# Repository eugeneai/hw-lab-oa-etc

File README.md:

# hw-lab-oa-etc
PCB for laboratory works on temerature sensor, generators and ADC, etc.

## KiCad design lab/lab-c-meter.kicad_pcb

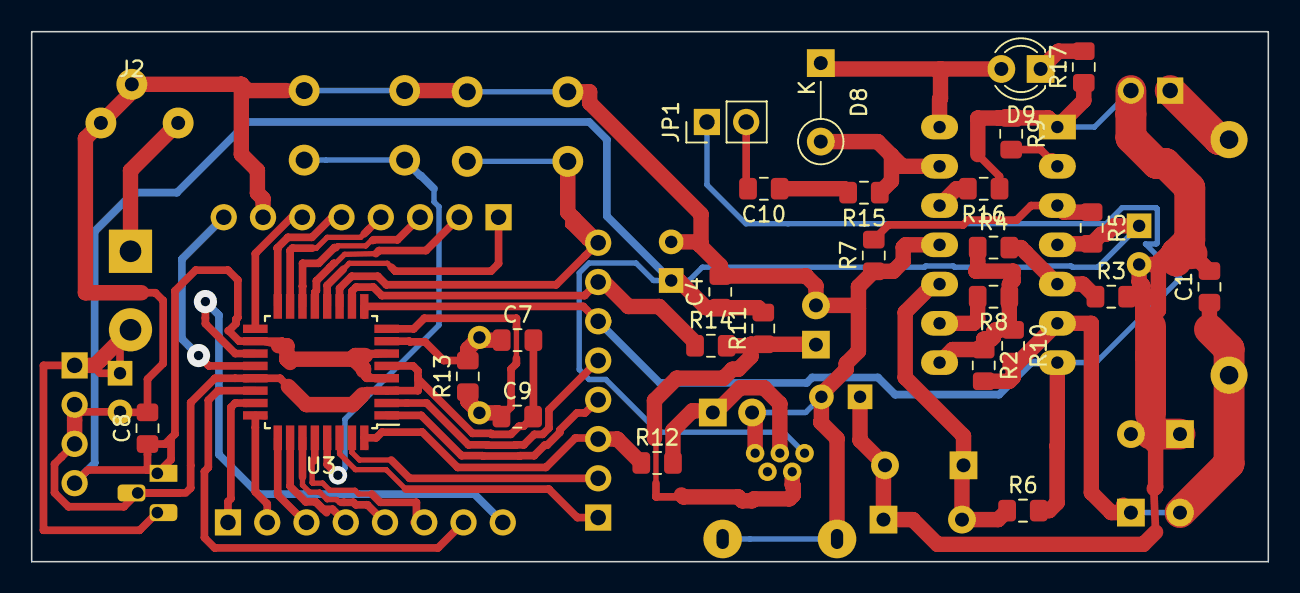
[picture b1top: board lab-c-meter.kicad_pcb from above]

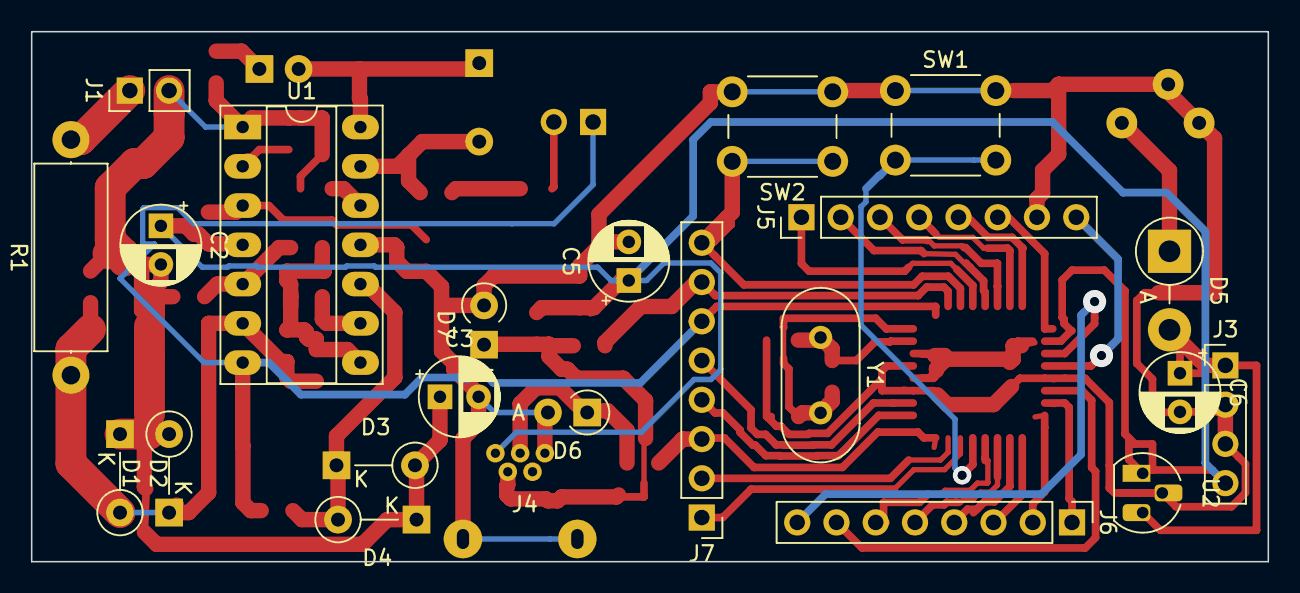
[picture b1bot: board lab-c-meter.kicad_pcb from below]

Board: 2 copper layers, 80.0 x 34.3 mm, 50 parts (23 on the bottom side), 47 nets.

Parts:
C1: 22n; C_0805_2012Metric_Pad1.15x1.40mm_HandSolder
C2, C3: 220u 6.3V; CP_Radial_D5.0mm_P2.50mm
C4, C8, C10: 100n; C_0805_2012Metric_Pad1.15x1.40mm_HandSolder
C5, C6: 4u7 6.3V; CP_Radial_D5.0mm_P2.50mm
C7, C9: 22p; C_0805_2012Metric_Pad1.15x1.40mm_HandSolder
D1, D2: HER105; D_A-405_P5.08mm_Vertical_KathodeUp
D3, D4, D8: 4148; D_A-405_P5.08mm_Vertical_KathodeUp
D5: M7; D_5W_P5.08mm_Vertical_AnodeUp
D6: 3v6; D_A-405_P2.54mm_Vertical_AnodeUp
D7: 3v6; D_A-405_P2.54mm_Vertical_KathodeUp
D9: AC; LED_D3.0mm
J1: IN; PinHeader_1x02_P2.54mm_Vertical
J2: Barrel_Jack_Switch; Barrel-little-11mm-x-5mm
J3: Conn_01x04; PinHeader_1x04_P2.54mm_Vertical
J4: USB_B_Mini; USB-mini-S2126.12010-Circular
J5: PB; PinHeader_1x08_P2.54mm_Vertical
J6: PC; PinHeader_1x08_P2.54mm_Vertical
J7: PD; PinHeader_1x08_P2.54mm_Vertical
JP1: WATCH; PinHeader_1x02_P2.54mm_Vertical
R1: 0.33 0.5W; R_Axial_DIN0414_L11.9mm_D4.5mm_P15.24mm_Horizontal
R2: 3K3; R_0805_2012Metric_Pad1.15x1.40mm_HandSolder
R3: 11K; R_0805_2012Metric_Pad1.15x1.40mm_HandSolder
R4, R5, R7: 100K; R_0805_2012Metric_Pad1.15x1.40mm_HandSolder
R6: 10K; R_0805_2012Metric_Pad1.15x1.40mm_HandSolder
R8, R9, R16: 4K7; R_0805_2012Metric_Pad1.15x1.40mm_HandSolder
R10: 1K0; R_0805_2012Metric_Pad1.15x1.40mm_HandSolder
R11: 1k5; R_0805_2012Metric_Pad1.15x1.40mm_HandSolder
R12, R14: 68R; R_0805_2012Metric_Pad1.15x1.40mm_HandSolder
R13: 1M; R_0805_2012Metric_Pad1.15x1.40mm_HandSolder
R15: 10k; R_0805_2012Metric_Pad1.15x1.40mm_HandSolder
R17: 10R; R_0805_2012Metric_Pad1.15x1.40mm_HandSolder
SW1: RST; SW_PUSH_6mm
SW2: BLD; SW_PUSH_6mm
U1: LM324; DIP-14_W7.62mm_Socket_LongPads
U2: L78L05_TO92; TO-92_HandSolder
U3: ATmega8-16AU; TQFP-32_7x7mm_P0.8mm
Y1: 16MHz; Crystal_HC49-U_Vertical

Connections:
+5V: C2.1, C4.1, C5.1, C8.1, J3.4, J4.1, R5.2, R11.2, U1.4, U2.1, U3.4, U3.6, U3.18
ADC6: J6.8, U3.19
ADC7: J6.7, U3.22
AREF: J5.8, U3.20
CNT: J7.6, JP1.1, R6.2, U1.7, U3.9
D+: J7.3, R12.1, U3.32
D-: J7.7, R14.1, U3.10
GND: C3.2, C4.2, C5.2, C6.2, C7.2, C8.2, C9.2, D6.2, D7.2, J2.2, J2.3, J3.2, J3.3, J4.5, J4.6, J5.7, R7.1, SW1.1, SW2.2, U1.11, U2.2, U3.3, U3.5, U3.21
MID: C1.2, C2.2, C3.1, D1.2, D2.1, D3.2, D4.1, J1.2, R3.2, R9.1, R16.1, R17.1, U1.1
MISO: J5.5, U3.16
MOSI: J5.4, U3.15
unnamed: C1.1, D1.1, D2.2, R1.1, R2.2, R10.2, U1.6
unnamed: C7.1, R13.2, U3.7, Y1.1
unnamed: C9.1, R13.1, U3.8, Y1.2
unnamed: C10.1, R15.2
unnamed: C10.2, JP1.2
unnamed: D3.1, D4.2, R6.1, U1.10
unnamed: D5.1, J2.1
unnamed: D6.1, J4.3, R12.2
unnamed: D7.1, J4.2, R11.1, R14.2
unnamed: D8.1, D9.2, U1.14
unnamed: D8.2, R15.1, U1.13
unnamed: D9.1, R17.2
unnamed: J1.1, R1.2
unnamed: J5.1, U3.12
unnamed: J5.2, U3.13
unnamed: R3.1, R4.2, U1.5
unnamed: R5.1, R7.2, U1.3
unnamed: R8.2, U1.9
unnamed: R9.2, U1.2
unnamed: R2.1, R4.1, R8.1, R10.1, U1.8
unnamed: R16.2, U1.12
PC0: J6.1, U3.23
PC1: J6.2, U3.24
PC2: J6.3, U3.25
PC3: J6.4, U3.26
PC4: J6.5, U3.27
PC5: J6.6, U3.28
PD0: J7.1, U3.30
PD1: J7.2, U3.31
PD3: J7.4, U3.1
PD4: J7.5, U3.2
PD7: J7.8, SW2.1, U3.11
SCK: J5.6, U3.17
SS: J5.3, U3.14
VIN: C6.1, D5.2, J3.1, U2.3
~RESET: SW1.2, U3.29

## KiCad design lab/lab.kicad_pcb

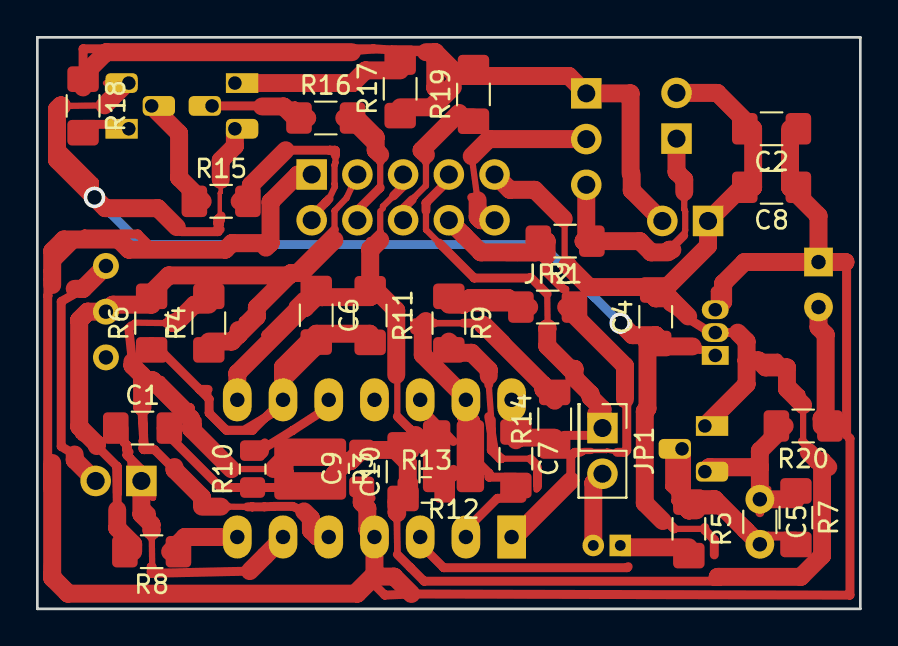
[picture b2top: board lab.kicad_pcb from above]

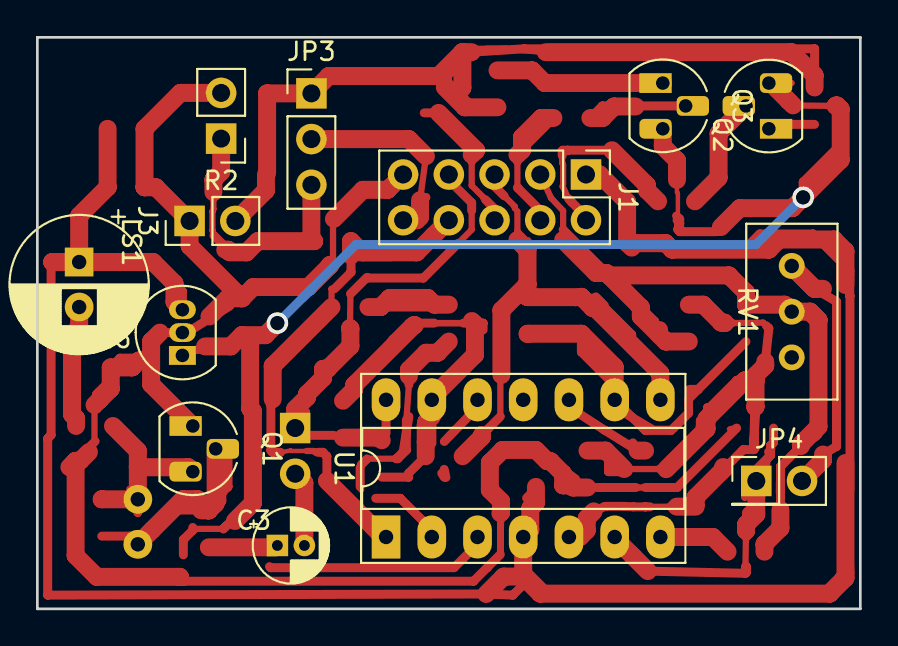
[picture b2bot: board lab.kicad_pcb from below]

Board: 2 copper layers, 45.7 x 31.8 mm, 43 parts (13 on the bottom side), 31 nets.

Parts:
C1, C2, C4: 1u; C_1206_3216Metric_Pad1.42x1.75mm_HandSolder
C3: 5u 5V; CP_Radial_D4.0mm_P1.50mm
C5: 6u8; C_Disc_D3.0mm_W1.6mm_P2.50mm
C6: 33n; C_1206_3216Metric_Pad1.42x1.75mm_HandSolder
C7: 10n; C_1206_3216Metric_Pad1.42x1.75mm_HandSolder
C8, C10: 100n; C_1206_3216Metric_Pad1.42x1.75mm_HandSolder
C9: 100n; C_0805_2012Metric_Pad1.15x1.40mm_HandSolder
J1: FACE; PinHeader_2x05_P2.54mm_Vertical
J3: C?; PinHeader_1x02_P2.54mm_Vertical
JP1: VIS; PinHeader_2x01_P2.54mm_Vertical
JP2: 0R; R_1206_3216Metric_Pad1.42x1.75mm_HandSolder
JP3: MWHAT; PinHeader_1x03_P2.54mm_Vertical
JP4: GEN; PinHeader_2x01_P2.54mm_Vertical
LS1: Piezo; CP_Radial_D7.5mm_P2.50mm
Q1, Q2, Q3: Q_NPN_EBC; TO-92_HandSolder
R1: 2K2; R_1206_3216Metric_Pad1.42x1.75mm_HandSolder
R2: SIL; PinHeader_1x02_P2.54mm_Vertical
R3: 22K; R_0815_2038Metric_Pad1.53x4.00mm_HandSolder
R4, R11: 100K; R_1206_3216Metric_Pad1.42x1.75mm_HandSolder
R5, R17: 1K; R_1206_3216Metric_Pad1.42x1.75mm_HandSolder
R6, R15, R16, R18: 10K; R_1206_3216Metric_Pad1.42x1.75mm_HandSolder
R7: 30K; R_1206_3216Metric_Pad1.42x1.75mm_HandSolder
R8, R20: 0R; R_1206_3216Metric_Pad1.42x1.75mm_HandSolder
R9: 4K7; R_1206_3216Metric_Pad1.42x1.75mm_HandSolder
R10: 10K; R_0805_2012Metric_Pad1.15x1.40mm_HandSolder
R12: 100K; R_0815_2038Metric_Pad1.53x4.00mm_HandSolder
R13: 100K; R_0805_2012Metric_Pad1.15x1.40mm_HandSolder
R14: 220K; R_1206_3216Metric_Pad1.42x1.75mm_HandSolder
R19: 220R; R_1206_3216Metric_Pad1.42x1.75mm_HandSolder
RV1: 100K; Potentiometer_Bourns_3296W_Vertical
U1: LM324; DIP-14_W7.62mm_Socket_LongPads
U2: L78L33_TO92; TO-92_Inline

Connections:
3V3: C4.1, Q2.3, Q3.3, U1.3, U2.1
+5V: C2.1, C8.1, C9.1, J1.1, LS1.1, U1.4, U2.3
-5V: C10.2, U1.11
CMEAS: J3.2, JP3.1, R17.1, R18.1, R19.2
CMRST: J1.6, R19.1
CSD1: J1.2, R15.2
CSD2: J1.4, R16.2
GNDD: C1.2, C2.2, C4.2, C8.2, C9.2, C10.1, J1.9, J3.1, Q1.1, R2.2, R3.2, R10.1, R13.1, U2.2
MEAS: J1.10, JP3.2
unnamed: C1.1, JP4.1, U1.6
unnamed: C3.1, R5.2
unnamed: C3.2, JP1.2
unnamed: C5.1, Q1.3, R7.1, R20.2
unnamed: C5.2, Q1.2, R5.1, R7.2
unnamed: C6.2, R6.1, R11.2, U1.9
unnamed: C7.2, R12.1, R14.2, U1.13
unnamed: JP4.2, RV1.1
unnamed: LS1.2, R20.1
unnamed: Q2.1, R18.2
unnamed: Q2.2, R15.1
unnamed: Q3.1, R17.2
unnamed: Q3.2, R16.1
unnamed: R3.1, R4.2, U1.5
unnamed: R9.2, U1.2
unnamed: R10.2, U1.10
unnamed: R13.2, U1.12
SIN: C7.1, J1.7, JP1.1, R14.1, U1.14
SQUARE: J1.3, R4.1, R6.2, R8.1, R8.2, RV1.2, U1.7
TMEAS: JP3.3, R1.1, R2.1
TRIANGLE: C6.1, J1.5, R11.1, R12.2, U1.8
VREF3.3: J1.8, JP2.1, JP2.2, R1.2, R9.1, U1.1

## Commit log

2019-02-09 Initial import
2019-02-09 New design almost without jumpers.
2019-02-09 Added README
2019-02-11 Made a final design.
2019-02-11 Finalized gerber generation
2019-02-11 Remembered how to make holes
2019-02-11 Turned IC to bask
2019-02-11 Final PCB
2019-02-11 TopoR state.
2019-02-12 Fill more space with Cu.
2019-02-14 Removed wrong parts. Remade PCB. Too thick.
2019-02-15 Added thick tracks.
2019-02-15 Local store
2019-02-16 The current state.
2019-02-26 as of today
2019-02-26 Added C measuring kernel.
2019-02-27 Added ATmega8
2019-02-27 Added elements to PCB
2019-02-27 Expanded the PCB
2019-02-27 Finished
2019-02-27 Added topoR proj
2019-02-28 Production
2019-03-01 Shifted top level for buttons.
2019-03-01 Corrected HW errors.
2019-03-03 Added AO book and AC Voltage detector.
2019-03-04 Added a jumper breaking tester
2019-03-04 Make vias bigger.
2019-03-04 Local commit
2019-03-05 Added calculation.
2019-03-05 Setup serials.
2019-03-05 Added ignore list
2019-03-05 Added serial reader.
2019-03-05 Added timer setups.
2019-03-05 Implemented counters by times and outer timing.
2019-03-07 Added UART implementation for atmega8
2019-03-07 Ported to atmega8 pulse counter.
2019-03-08 Exploring raw data.
